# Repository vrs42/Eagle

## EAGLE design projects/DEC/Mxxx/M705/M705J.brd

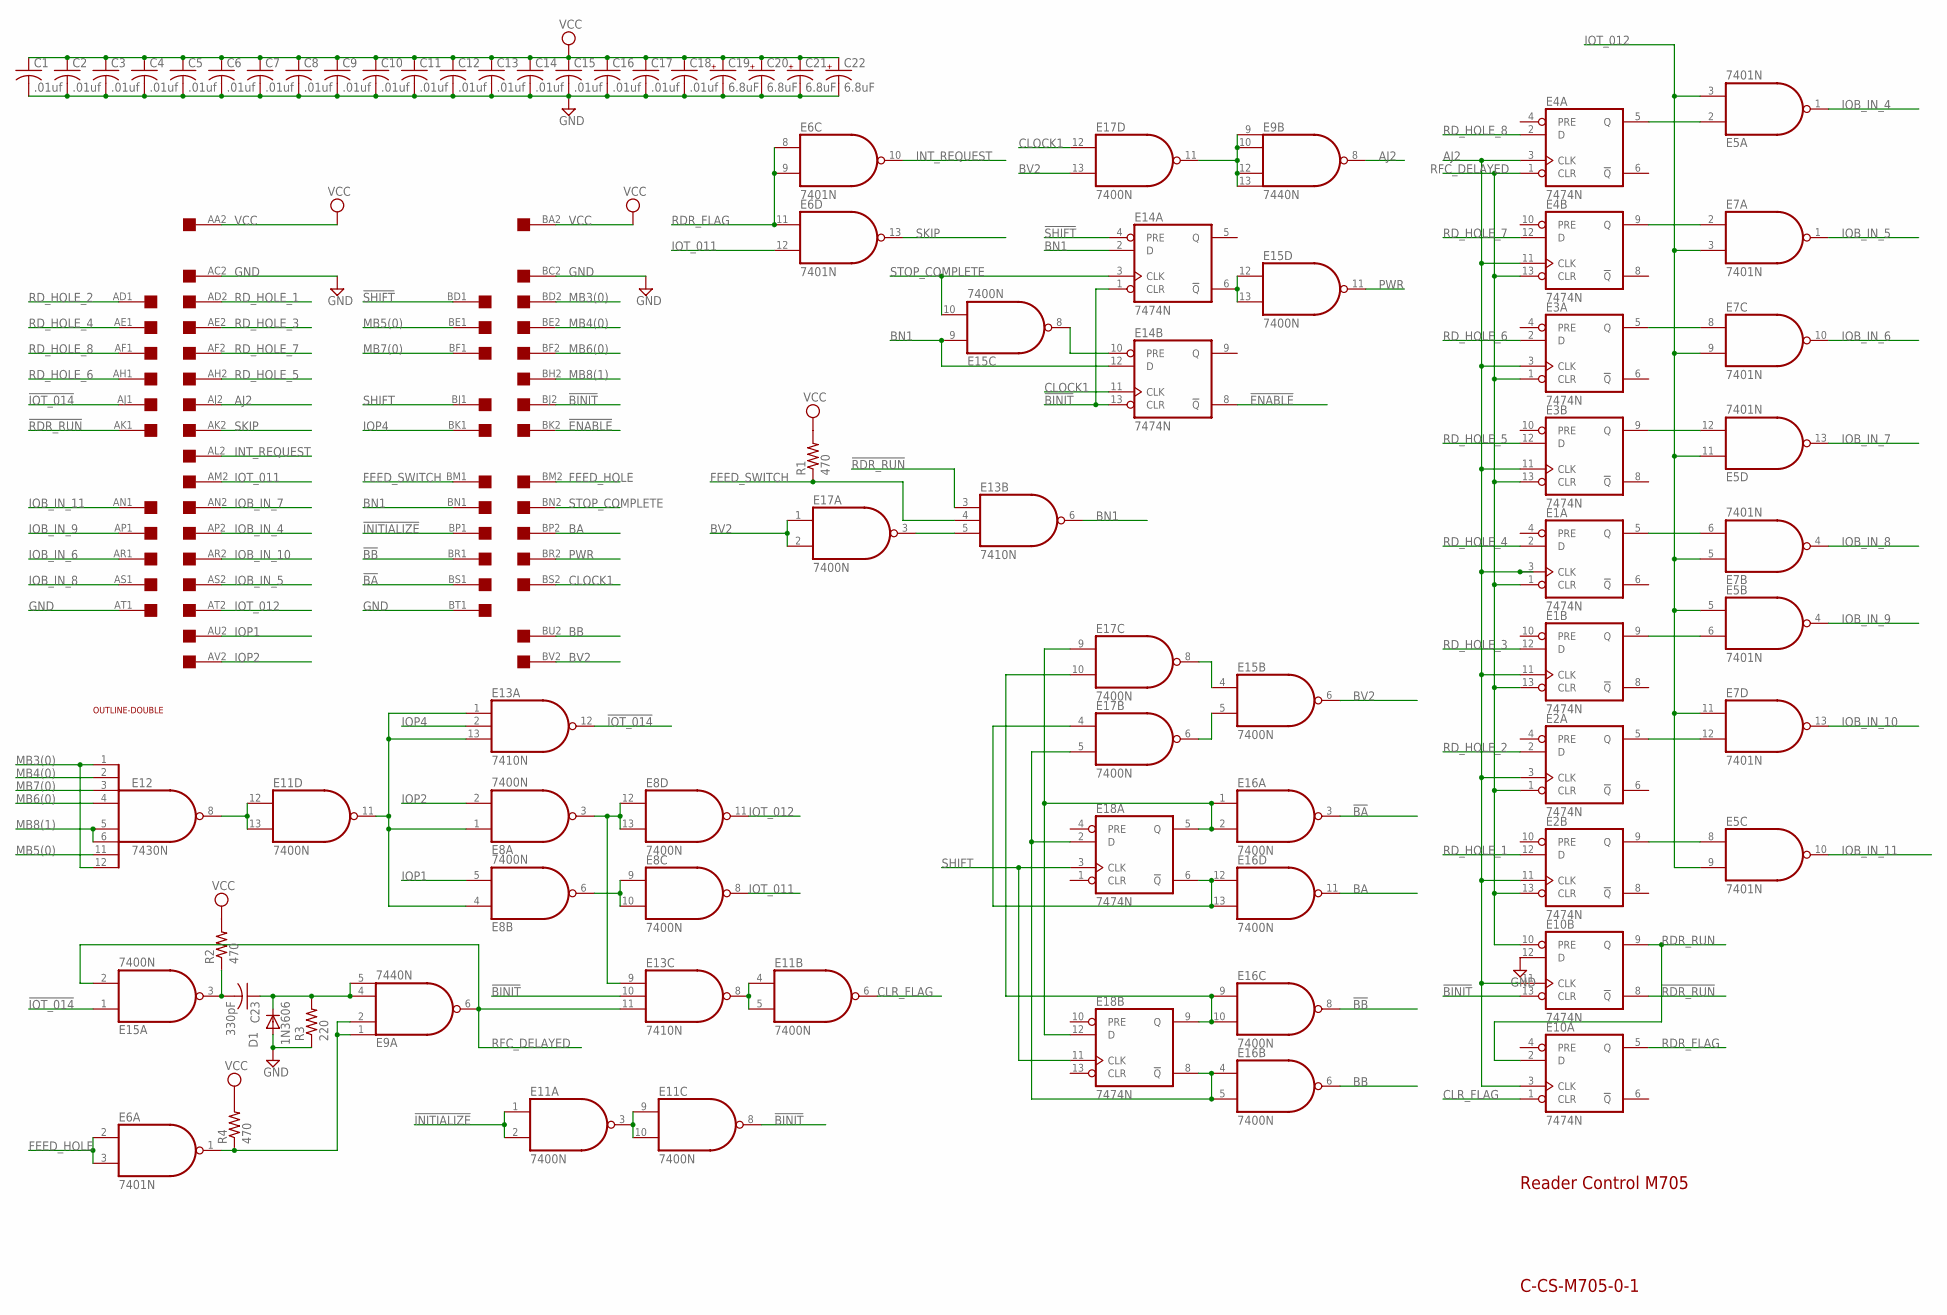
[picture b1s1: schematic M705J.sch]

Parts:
C1, C2, C3, C4, C5, C6, C7, C8, C9, C10, C11, C12, C13, C14, C15, C16, C17, C18: .01uf; C075-032X103
C19, C20, C21, C22: 6.8uF; E12-8
C23: 330pF; C075-032X103
D1: 1N3606; DO35-10
E1, E2, E3, E4, E10, E14, E18: 7474N; DIL14
E5, E6, E7: 7401N; DIL14
E8, E11, E15, E16, E17: 7400N; DIL14
E9: 7440N; DIL14
E12: 7430N; DIL14
E13: 7410N; DIL14
R1, R2, R4: 470; 0207/10
R3: 220; 0207/10
U$5: DOUBLE; EDGE-CON4
U$6: OUTLINE-DOUBLE; DOUBLE

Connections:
!BA: E16.3 (O), U$5.BS1
!BB: E16.8 (O), U$5.BR1
!BINIT: E10.13 (CLR), E11.8 (O), E13.10 (I1), E14.1 (CLR), E14.13 (CLR), U$5.BJ2
!ENABLE: E14.8 (!Q), U$5.BK2
!INITIALIZE: E11.1 (I0), E11.2 (I1), U$5.BP1
!IOT_014: E13.12 (O), E15.1 (I0), U$5.AJ1
!RDR_RUN: E10.8 (!Q), E13.3 (I0), U$5.AK1
!SHIFT: E14.4 (PRE), U$5.BD1
AJ2: E1.3 (CLK), E1.11 (CLK), E2.3 (CLK), E2.11 (CLK), E3.3 (CLK), E3.11 (CLK), E4.3 (CLK), E4.11 (CLK), E9.8 (O), E10.3 (CLK), E10.11 (CLK), U$5.AJ2
BA: E16.11 (O), U$5.BP2
BB: E16.6 (O), U$5.BU2
BN1: E13.6 (O), E14.2 (D), E14.12 (D), E15.9 (I0), U$5.BN1
BV2: E15.6 (O), E17.1 (I0), E17.2 (I1), E17.13 (I1), U$5.BV2
CLOCK1: E14.11 (CLK), E17.12 (I0), U$5.BS2
CLR_FLAG: E10.1 (CLR), E11.6 (O)
FEED_HOLE: E6.2 (I0), E6.3 (I1), U$5.BM2
FEED_SWITCH: E13.4 (I1), R1.1, U$5.BM1
GND: C1.2, C2.2, C3.2, C4.2, C5.2, C6.2, C7.2, C8.2, C9.2, C10.2, C11.2, C12.2, C13.2, C14.2, C15.2, C16.2, C17.2, C18.2, C19.-, C20.-, C21.-, C22.-, D1.A, E1.7 (GND), E2.7 (GND), E3.7 (GND), E4.7 (GND), E5.7 (GND), E6.7 (GND), E7.7 (GND), E8.7 (GND), E9.7 (GND), E10.7 (GND), E10.12 (D), E11.7 (GND), E12.7 (GND), E13.7 (GND), E14.7 (GND), E15.7 (GND), E16.7 (GND), E17.7 (GND), E18.7 (GND), R3.1, U$5.AC2, U$5.AT1, U$5.BC2, U$5.BT1
INT_REQUEST: E6.10 (O), U$5.AL2
IOB_IN_4: E5.1 (O), U$5.AP2
IOB_IN_5: E7.1 (O), U$5.AS2
IOB_IN_6: E7.10 (O), U$5.AR1
IOB_IN_7: E5.13 (O), U$5.AN2
IOB_IN_8: E7.4 (O), U$5.AS1
IOB_IN_9: E5.4 (O), U$5.AP1
IOB_IN_10: E7.13 (O), U$5.AR2
IOB_IN_11: E5.10 (O), U$5.AN1
IOP1: E8.5 (I1), U$5.AU2
IOP2: E8.2 (I1), U$5.AV2
IOP4: E13.2 (I1), U$5.BK1
IOT_011: E6.12 (I1), E8.8 (O), U$5.AM2
IOT_012: E5.3 (I1), E5.5 (I0), E5.9 (I1), E5.11 (I0), E7.3 (I1), E7.5 (I0), E7.9 (I1), E7.11 (I0), E8.11 (O), U$5.AT2
MB3(0): E12.1 (I0), E12.12 (I7), U$5.BD2
MB4(0): E12.2 (I1), U$5.BE2
MB5(0): E12.11 (I6), U$5.BE1
MB6(0): E12.4 (I3), U$5.BF2
MB7(0): E12.3 (I2), U$5.BF1
MB8(1): E12.5 (I4), E12.6 (I5), U$5.BH2
unnamed: E16.9 (I0), E16.10 (I1), E17.10 (I1), E18.9 (Q)
unnamed: E4.5 (Q), E5.2 (I0)
unnamed: E4.9 (Q), E7.2 (I0)
unnamed: E16.12 (I0), E16.13 (I1), E17.4 (I0), E18.6 (!Q)
unnamed: E11.12 (I0), E11.13 (I1), E12.8 (O)
unnamed: E8.3 (O), E8.12 (I0), E8.13 (I1), E13.9 (I0)
unnamed: E8.6 (O), E8.9 (I0), E8.10 (I1)
unnamed: E8.1 (I0), E8.4 (I0), E11.11 (O), E13.1 (I0), E13.13 (I2)
unnamed: E3.5 (Q), E7.8 (I0)
unnamed: E3.9 (Q), E5.12 (I1)
unnamed: E1.5 (Q), E7.6 (I1)
unnamed: E1.9 (Q), E5.6 (I1)
unnamed: E2.5 (Q), E7.12 (I1)
unnamed: E2.9 (Q), E5.8 (I0)
unnamed: E16.4 (I0), E16.5 (I1), E17.5 (I1), E18.2 (D), E18.8 (!Q)
unnamed: E16.1 (I0), E16.2 (I1), E17.9 (I0), E18.5 (Q), E18.12 (D)
unnamed: E15.4 (I0), E17.8 (O)
unnamed: E15.5 (I1), E17.6 (O)
unnamed: E9.9 (I0), E9.10 (I1), E9.12 (I2), E9.13 (I3), E17.11 (O)
unnamed: E14.6 (!Q), E15.12 (I0), E15.13 (I1)
unnamed: E14.10 (PRE), E15.8 (O)
unnamed: C23.2, E15.3 (O), R2.1
unnamed: C23.1, D1.C, E9.4 (I2), E9.5 (I3), R3.2
unnamed: E6.1 (O), E9.1 (I0), E9.2 (I1), R4.1
unnamed: E11.3 (O), E11.9 (I0), E11.10 (I1)
unnamed: E11.4 (I0), E11.5 (I1), E13.8 (O)
unnamed: E13.5 (I2), E17.3 (O)
PWR: E15.11 (O), U$5.BR2
RDR_FLAG: E6.8 (I0), E6.9 (I1), E6.11 (I0), E10.5 (Q)
RDR_RUN: E10.2 (D), E10.9 (Q)
RD_HOLE_1: E2.12 (D), U$5.AD2
RD_HOLE_2: E2.2 (D), U$5.AD1
RD_HOLE_3: E1.12 (D), U$5.AE2
RD_HOLE_4: E1.2 (D), U$5.AE1
RD_HOLE_5: E3.12 (D), U$5.AH2
RD_HOLE_6: E3.2 (D), U$5.AH1
RD_HOLE_7: E4.12 (D), U$5.AF2
RD_HOLE_8: E4.2 (D), U$5.AF1
RFC_DELAYED: E1.1 (CLR), E1.13 (CLR), E2.1 (CLR), E2.13 (CLR), E3.1 (CLR), E3.13 (CLR), E4.1 (CLR), E4.13 (CLR), E9.6 (O), E10.10 (PRE), E13.11 (I2), E15.2 (I1)
SHIFT: E18.3 (CLK), E18.11 (CLK), U$5.BJ1
SKIP: E6.13 (O), U$5.AK2
STOP_COMPLETE: E14.3 (CLK), E15.10 (I1), U$5.BN2
VCC: C1.1, C2.1, C3.1, C4.1, C5.1, C6.1, C7.1, C8.1, C9.1, C10.1, C11.1, C12.1, C13.1, C14.1, C15.1, C16.1, C17.1, C18.1, C19.+, C20.+, C21.+, C22.+, E1.14 (VCC), E2.14 (VCC), E3.14 (VCC), E4.14 (VCC), E5.14 (VCC), E6.14 (VCC), E7.14 (VCC), E8.14 (VCC), E9.14 (VCC), E10.14 (VCC), E11.14 (VCC), E12.14 (VCC), E13.14 (VCC), E14.14 (VCC), E15.14 (VCC), E16.14 (VCC), E17.14 (VCC), E18.14 (VCC), R1.2, R2.2, R4.2, U$5.AA2, U$5.BA2

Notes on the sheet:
C-CS-M705-0-1
Reader Control M705

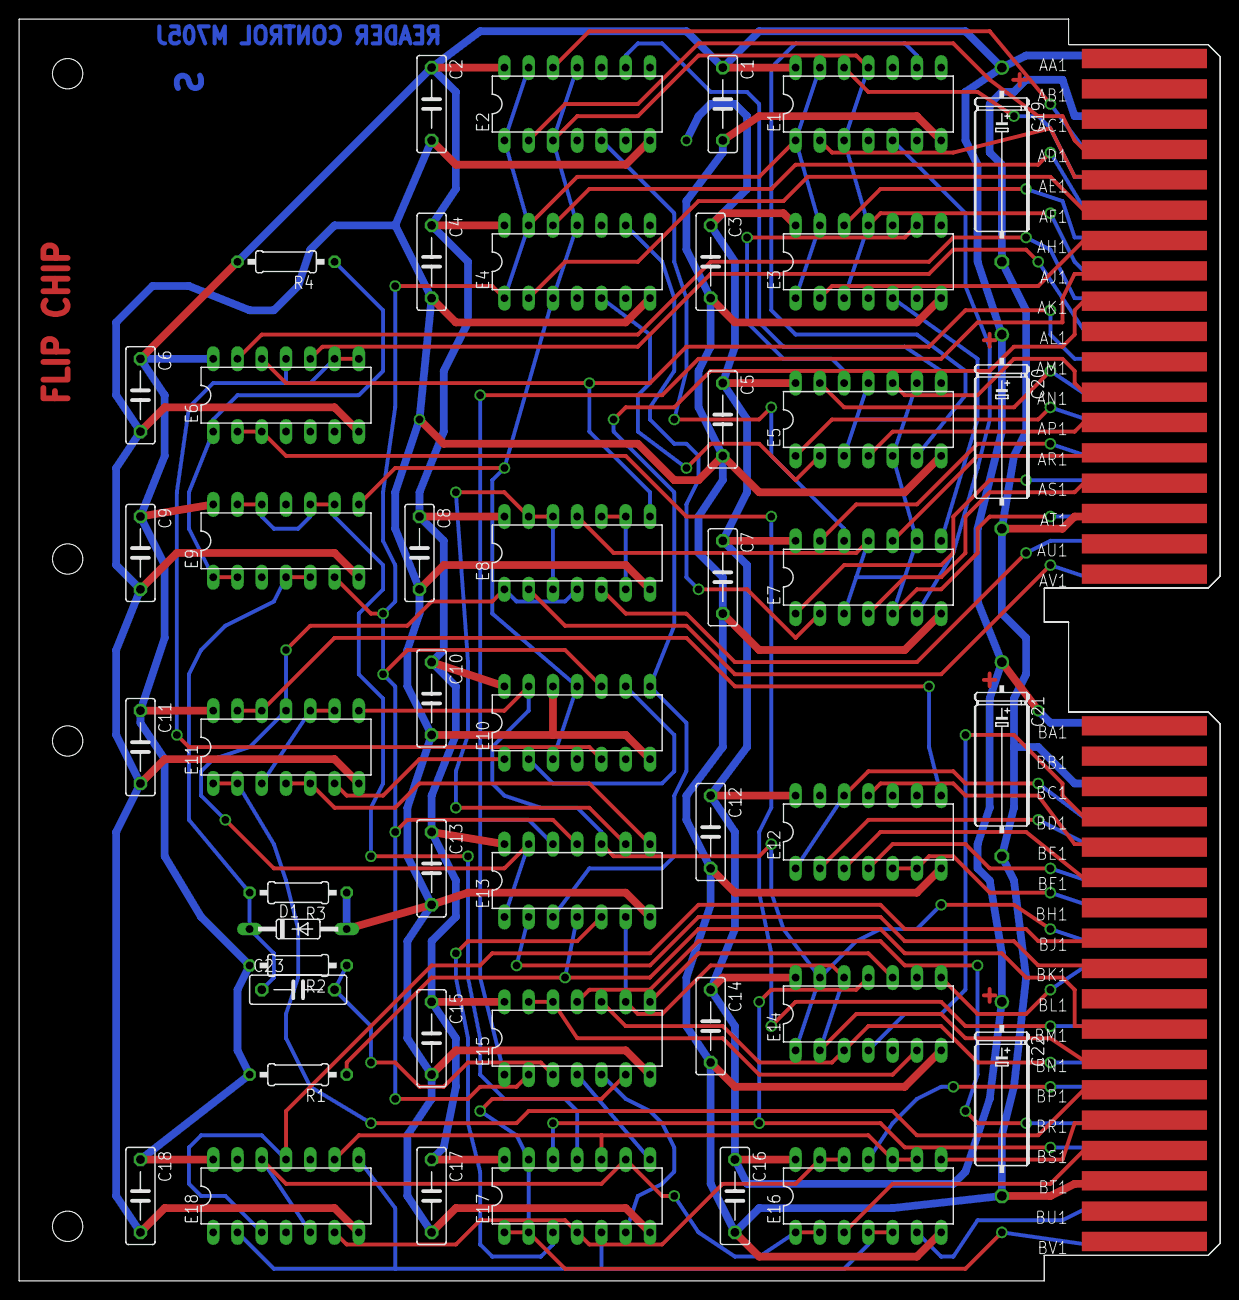
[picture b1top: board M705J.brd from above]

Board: 2 copper layers, 125.7 x 132.1 mm, 49 parts (0 on the bottom side), 81 nets.

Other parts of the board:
U$3: FLIPCHIP

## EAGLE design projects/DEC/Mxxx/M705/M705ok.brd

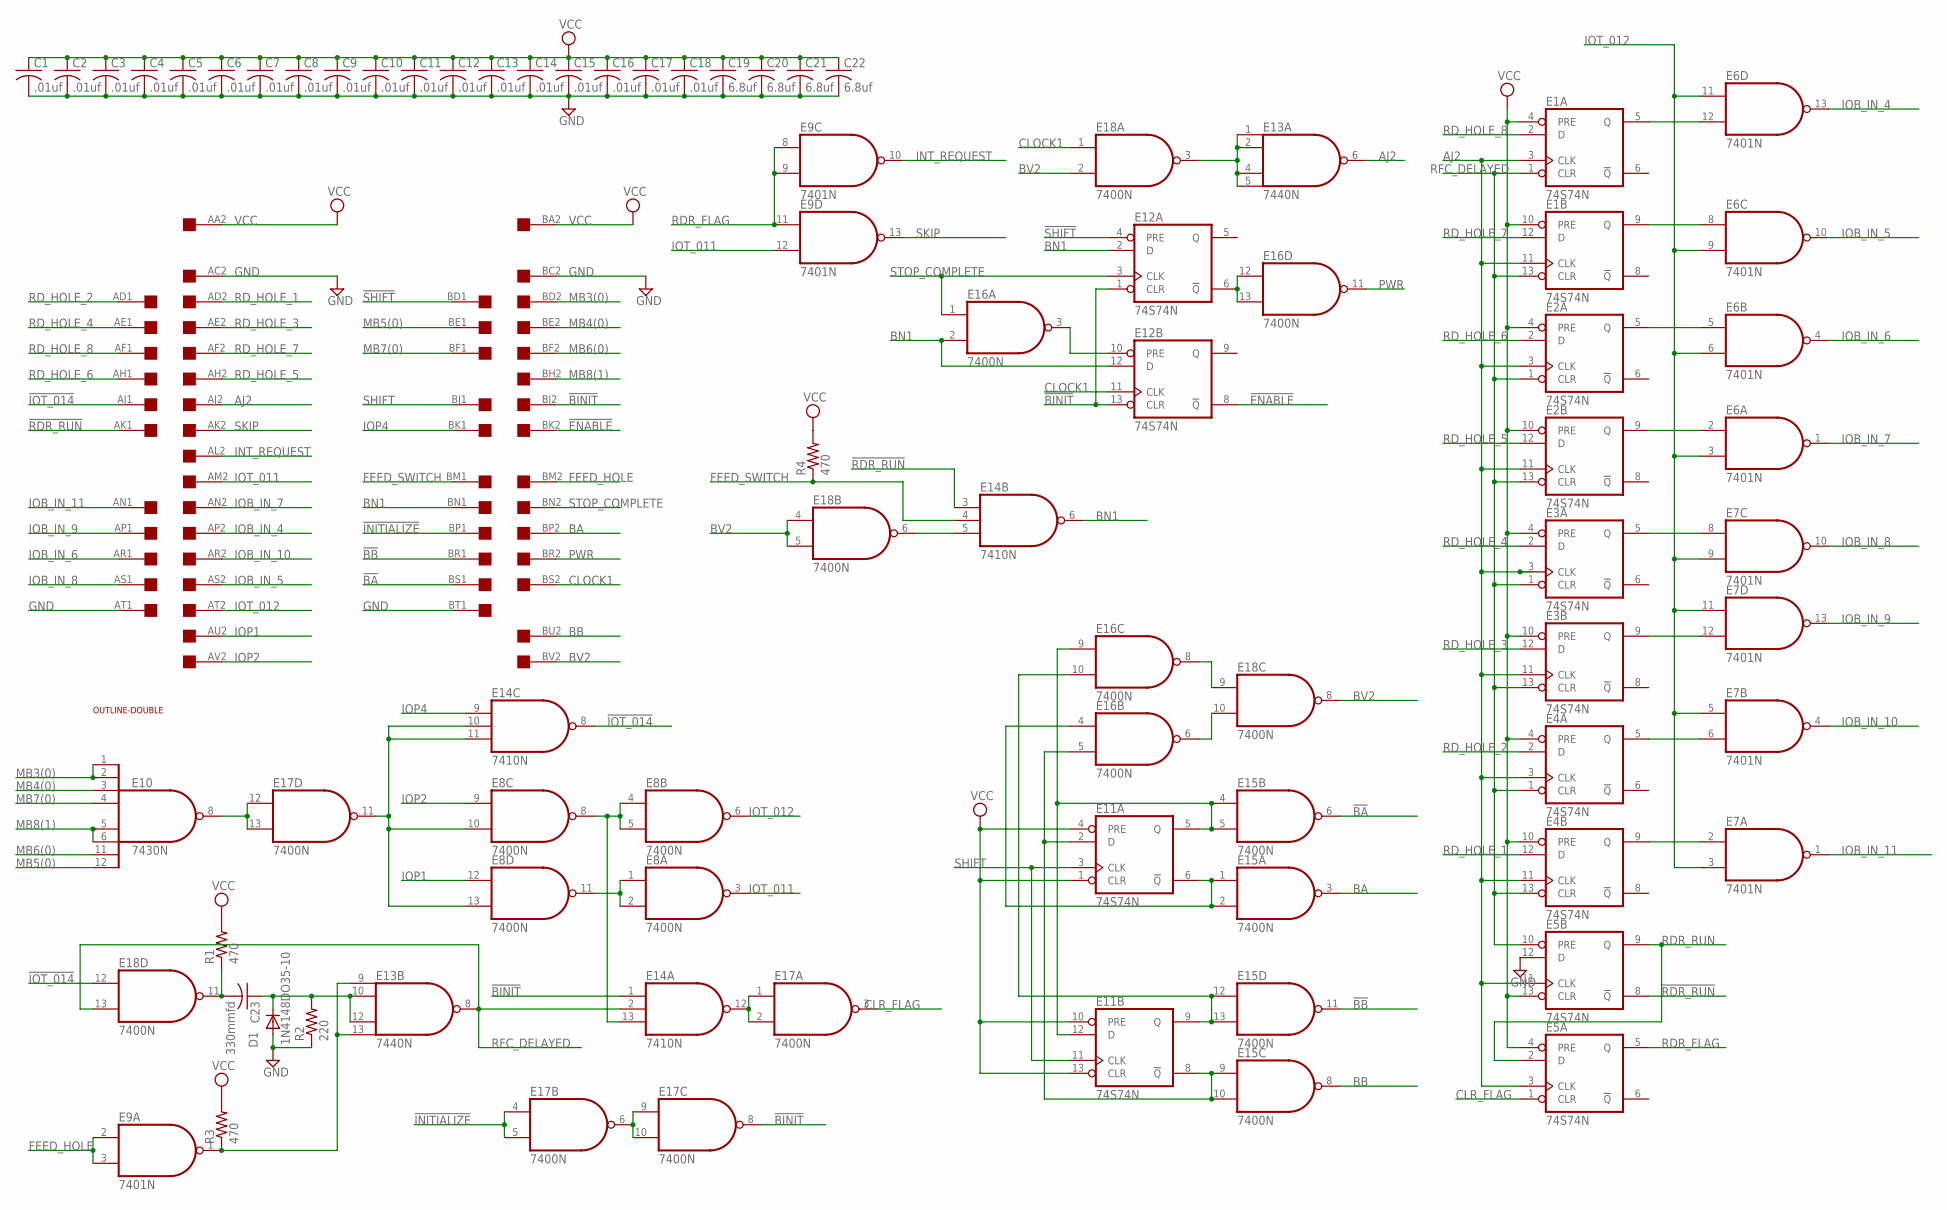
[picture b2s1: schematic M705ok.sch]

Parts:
C1, C2, C3, C4, C5, C6, C7, C8, C9, C10, C11, C12, C13, C14, C15, C16, C17, C18: .01uf; C050-025X075
C19, C20, C21, C22: 6.8uf; C150-054X183
C23: 330mmfd; C050-025X075
D1: 1N4148DO35-10; DO35-10
E1, E2, E3, E4, E5, E11, E12: 74S74N; DIL14
E6, E7, E9: 7401N; DIL14
E8, E15, E16, E17, E18: 7400N; DIL14
E10: 7430N; DIL14
E13: 7440N; DIL14
E14: 7410N; DIL14
R1, R3, R4: 470; 0207/10
R2: 220; 0207/10
U$5: DOUBLE; EDGE-CON4
U$6: OUTLINE-DOUBLE; DOUBLE

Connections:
!BA: E15.6 (O), U$5.BS1
!BB: E15.11 (O), U$5.BR1
!BINIT: E12.1 (CLR), E12.13 (CLR), E14.1 (I0), E17.8 (O), U$5.BJ2
!ENABLE: E12.8 (!Q), U$5.BK2
!INITIALIZE: E17.4 (I0), E17.5 (I1), U$5.BP1
!IOT_014: E14.8 (O), E18.12 (I0), U$5.AJ1
!RDR_RUN: E5.8 (!Q), E14.3 (I0), U$5.AK1
!SHIFT: E12.4 (PRE), U$5.BD1
AJ2: E1.3 (CLK), E1.11 (CLK), E2.3 (CLK), E2.11 (CLK), E3.3 (CLK), E3.11 (CLK), E4.3 (CLK), E4.11 (CLK), E5.3 (CLK), E5.11 (CLK), E13.6 (O), U$5.AJ2
BA: E15.3 (O), U$5.BP2
BB: E15.8 (O), U$5.BU2
BN1: E12.2 (D), E12.12 (D), E14.6 (O), E16.2 (I1), U$5.BN1
BV2: E18.2 (I1), E18.4 (I0), E18.5 (I1), E18.8 (O), U$5.BV2
CLOCK1: E12.11 (CLK), E18.1 (I0), U$5.BS2
CLR_FLAG: E5.1 (CLR), E17.3 (O)
FEED_HOLE: E9.2 (I0), E9.3 (I1), U$5.BM2
FEED_SWITCH: E14.4 (I1), R4.1, U$5.BM1
GND: C1.2, C2.2, C3.2, C4.2, C5.2, C6.2, C7.2, C8.2, C9.2, C10.2, C11.2, C12.2, C13.2, C14.2, C15.2, C16.2, C17.2, C18.2, C19.2, C20.2, C21.2, C22.2, D1.A, E1.7 (GND), E2.7 (GND), E3.7 (GND), E4.7 (GND), E5.7 (GND), E5.12 (D), E6.7 (GND), E7.7 (GND), E8.7 (GND), E9.7 (GND), E10.7 (GND), E11.7 (GND), E12.7 (GND), E13.7 (GND), E14.7 (GND), E15.7 (GND), E16.7 (GND), E17.7 (GND), E18.7 (GND), R2.1, U$5.AC2, U$5.AT1, U$5.BC2, U$5.BT1
INT_REQUEST: E9.10 (O), U$5.AL2
IOB_IN_4: E6.13 (O), U$5.AP2
IOB_IN_5: E6.10 (O), U$5.AS2
IOB_IN_6: E6.4 (O), U$5.AR1
IOB_IN_7: E6.1 (O), U$5.AN2
IOB_IN_8: E7.10 (O), U$5.AS1
IOB_IN_9: E7.13 (O), U$5.AP1
IOB_IN_10: E7.4 (O), U$5.AR2
IOB_IN_11: E7.1 (O), U$5.AN1
IOP1: E8.12 (I0), U$5.AU2
IOP2: E8.9 (I0), U$5.AV2
IOP4: E14.9 (I0), U$5.BK1
IOT_011: E8.3 (O), E9.12 (I1), U$5.AM2
IOT_012: E6.3 (I1), E6.6 (I1), E6.9 (I1), E6.11 (I0), E7.3 (I1), E7.5 (I0), E7.9 (I1), E7.11 (I0), E8.6 (O), U$5.AT2
MB3(0): E10.1 (I0), E10.2 (I1), U$5.BD2
MB4(0): E10.3 (I2), U$5.BE2
MB5(0): E10.12 (I7), U$5.BE1
MB6(0): E10.11 (I6), U$5.BF2
MB7(0): E10.4 (I3), U$5.BF1
MB8(1): E10.5 (I4), E10.6 (I5), U$5.BH2
unnamed: E1.5 (Q), E6.12 (I1)
unnamed: E1.9 (Q), E6.8 (I0)
unnamed: E11.6 (!Q), E15.1 (I0), E15.2 (I1), E16.4 (I0)
unnamed: E10.8 (O), E17.12 (I0), E17.13 (I1)
unnamed: E8.4 (I0), E8.5 (I1), E8.8 (O), E14.13 (I2)
unnamed: E8.1 (I0), E8.2 (I1), E8.11 (O)
unnamed: E8.10 (I1), E8.13 (I1), E14.10 (I1), E14.11 (I2), E17.11 (O)
unnamed: E2.5 (Q), E6.5 (I0)
unnamed: E2.9 (Q), E6.2 (I0)
unnamed: E3.5 (Q), E7.8 (I0)
unnamed: E3.9 (Q), E7.12 (I1)
unnamed: E4.5 (Q), E7.6 (I1)
unnamed: E4.9 (Q), E7.2 (I0)
unnamed: E11.5 (Q), E11.12 (D), E15.4 (I0), E15.5 (I1), E16.9 (I0)
unnamed: E11.9 (Q), E15.12 (I0), E15.13 (I1), E16.10 (I1)
unnamed: E11.2 (D), E11.8 (!Q), E15.9 (I0), E15.10 (I1), E16.5 (I1)
unnamed: E16.8 (O), E18.9 (I0)
unnamed: E16.6 (O), E18.10 (I1)
unnamed: E13.1 (I0), E13.2 (I1), E13.4 (I2), E13.5 (I3), E18.3 (O)
unnamed: E12.6 (!Q), E16.12 (I0), E16.13 (I1)
unnamed: E12.10 (PRE), E16.3 (O)
unnamed: C23.2, E18.11 (O), R1.1
unnamed: C23.1, D1.C, E13.10 (I1), E13.12 (I2), R2.2
unnamed: E9.1 (O), E13.9 (I0), E13.13 (I3), R3.1
unnamed: E17.6 (O), E17.9 (I0), E17.10 (I1)
unnamed: E14.12 (O), E17.1 (I0), E17.2 (I1)
unnamed: E14.5 (I2), E18.6 (O)
PWR: E16.11 (O), U$5.BR2
RDR_FLAG: E5.5 (Q), E9.8 (I0), E9.9 (I1), E9.11 (I0)
RDR_RUN: E5.2 (D), E5.9 (Q)
RD_HOLE_1: E4.12 (D), U$5.AD2
RD_HOLE_2: E4.2 (D), U$5.AD1
RD_HOLE_3: E3.12 (D), U$5.AE2
RD_HOLE_4: E3.2 (D), U$5.AE1
RD_HOLE_5: E2.12 (D), U$5.AH2
RD_HOLE_6: E2.2 (D), U$5.AH1
RD_HOLE_7: E1.12 (D), U$5.AF2
RD_HOLE_8: E1.2 (D), U$5.AF1
RFC_DELAYED: E1.1 (CLR), E1.13 (CLR), E2.1 (CLR), E2.13 (CLR), E3.1 (CLR), E3.13 (CLR), E4.1 (CLR), E4.13 (CLR), E5.10 (PRE), E13.8 (O), E14.2 (I1), E18.13 (I1)
SHIFT: E11.3 (CLK), E11.11 (CLK), U$5.BJ1
SKIP: E9.13 (O), U$5.AK2
STOP_COMPLETE: E12.3 (CLK), E16.1 (I0), U$5.BN2
VCC: C1.1, C2.1, C3.1, C4.1, C5.1, C6.1, C7.1, C8.1, C9.1, C10.1, C11.1, C12.1, C13.1, C14.1, C15.1, C16.1, C17.1, C18.1, C19.1, C20.1, C21.1, C22.1, E1.4 (PRE), E1.10 (PRE), E1.14 (VCC), E2.4 (PRE), E2.10 (PRE), E2.14 (VCC), E3.4 (PRE), E3.10 (PRE), E3.14 (VCC), E4.4 (PRE), E4.10 (PRE), E4.14 (VCC), E5.4 (PRE), E5.13 (CLR), E5.14 (VCC), E6.14 (VCC), E7.14 (VCC), E8.14 (VCC), E9.14 (VCC), E10.14 (VCC), E11.1 (CLR), E11.4 (PRE), E11.10 (PRE), E11.13 (CLR), E11.14 (VCC), E12.14 (VCC), E13.14 (VCC), E14.14 (VCC), E15.14 (VCC), E16.14 (VCC), E17.14 (VCC), E18.14 (VCC), R1.2, R3.2, R4.2, U$5.AA2, U$5.BA2

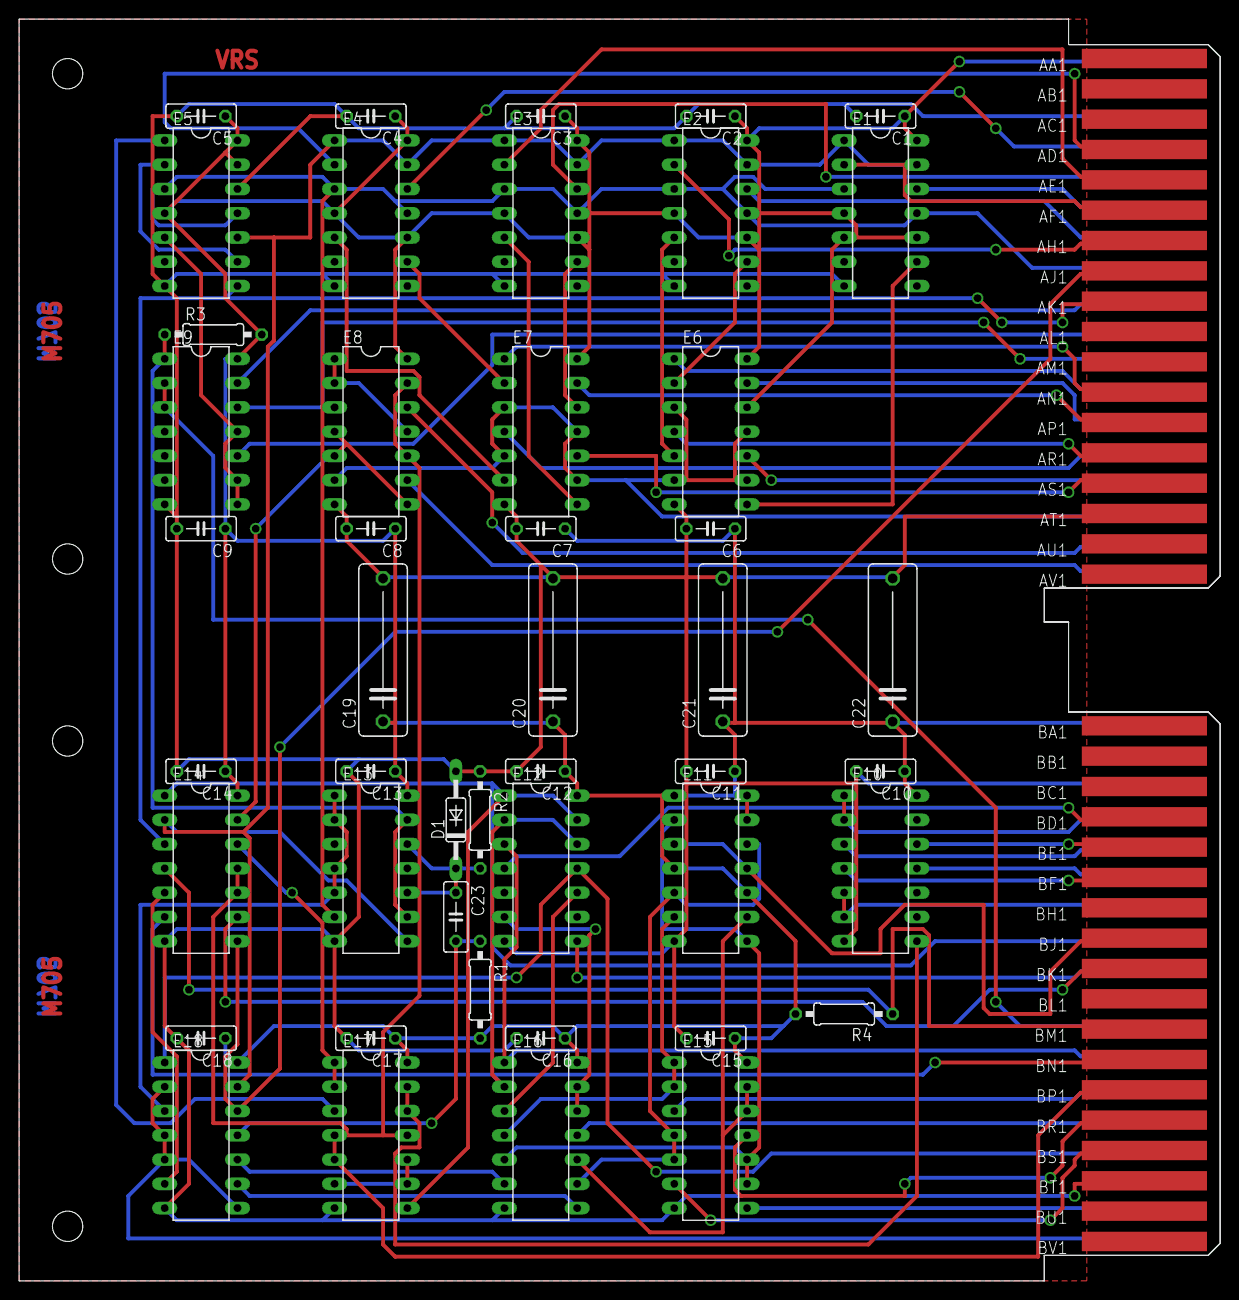
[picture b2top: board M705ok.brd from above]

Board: 2 copper layers, 125.7 x 132.1 mm, 48 parts (0 on the bottom side), 81 nets.

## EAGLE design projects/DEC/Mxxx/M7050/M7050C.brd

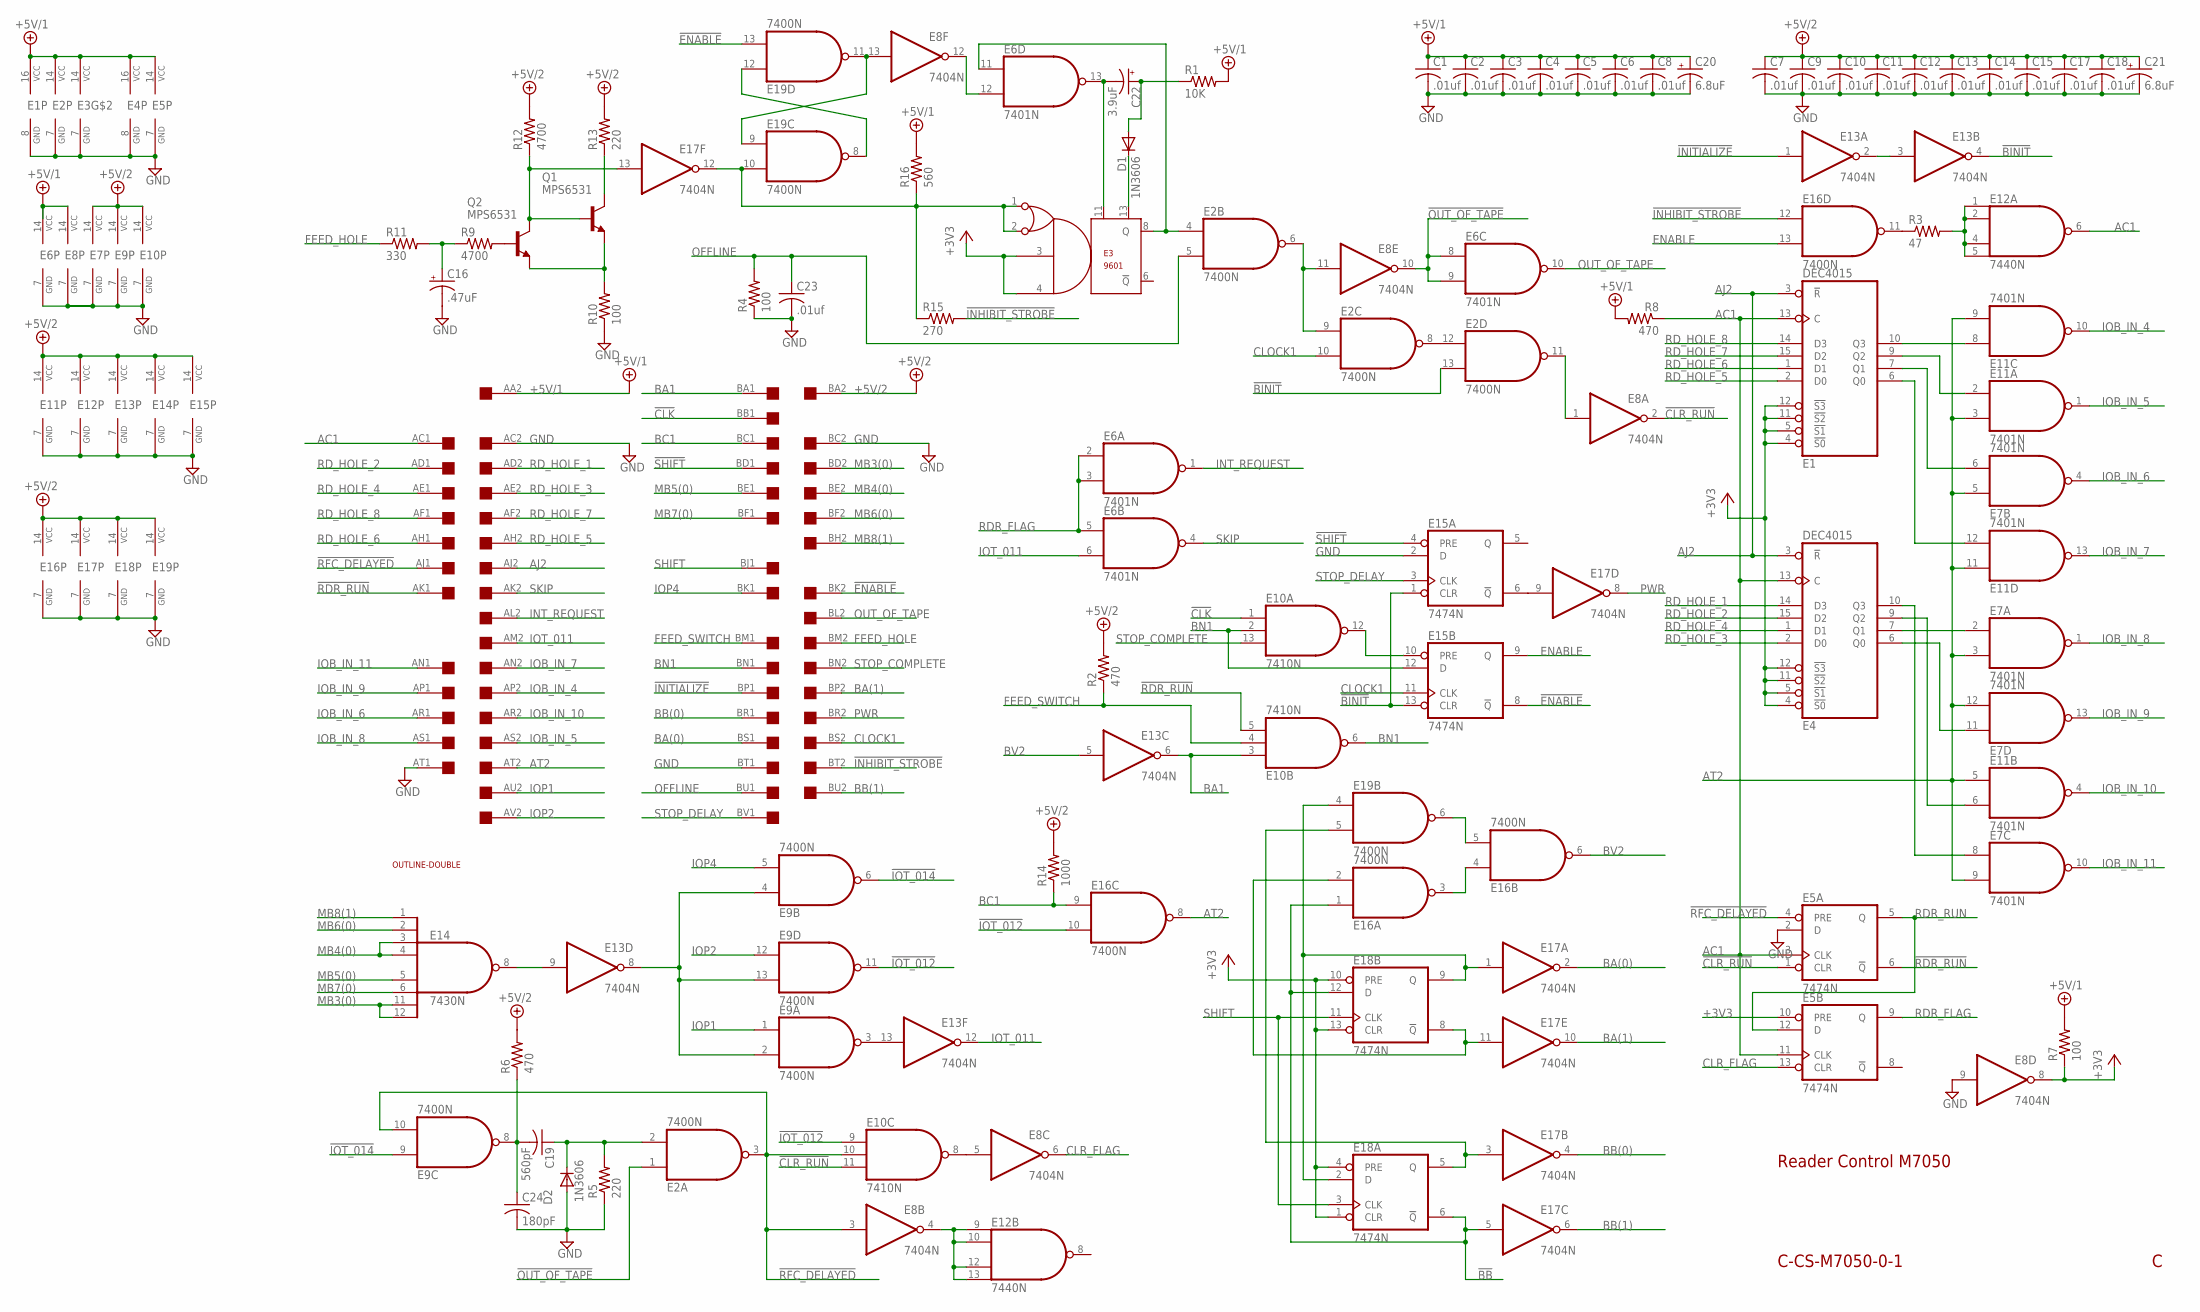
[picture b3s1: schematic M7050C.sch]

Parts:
C1, C2, C3, C4, C5, C6, C7, C8, C9, C10, C11, C12, C13, C14, C15, C17, C18, C23: .01uf; C075-032X103
C16: .47uF; E15-5
C19: 560pF; C075-032X103
C20, C21: 6.8uF; E12-8
C22: 3.9uF; E15-5
C24: 180pF; C075-032X103
D1, D2: 1N3606; DO35-10
E1, E4: DEC4015; DIL16
E2, E9, E16, E19: 7400N; DIL14
E3: 9601; DIL14
E5, E15, E18: 7474N; DIL14
E6, E7, E11: 7401N; DIL14
E8, E13, E17: 7404N; DIL14
E10: 7410N; DIL14
E12: 7440N; DIL14
E14: 7430N; DIL14
Q1, Q2: MPS6531; TO5
R1: 10K; 0207/10
R2, R6, R8: 470; 0207/10
R3: 47; 0207/10
R4, R7, R10: 100; 0207/10
R5, R13: 220; 0207/10
R9, R12: 4700; 0207/10
R11: 330; 0207/10
R14: 1000; 0207/10
R15: 270; 0207/10
R16: 560; 0207/10
U$5: DOUBLE; EDGE-CON4
U$6: OUTLINE-DOUBLE; DOUBLE

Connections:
!BA: E16.2 (I1), E17.11 (I), E18.8 (!Q)
!BB: E16.1 (I0), E17.5 (I), E18.6 (!Q), E18.12 (D)
!BINIT: E2.13 (I1), E13.4 (O), E15.1 (CLR), E15.13 (CLR)
!CLK: E10.1 (I0), U$5.BB1
!CLR_RUN: E5.1 (CLR), E8.2 (O), E10.11 (I2)
!ENABLE: E15.8 (!Q), E19.13 (I1), U$5.BK2
!INHIBIT_STROBE: E16.12 (I0), R15.2, U$5.BT2
!INITIALIZE: E13.1 (I), U$5.BP1
!IOT_011: E9.3 (O), E13.13 (I)
!IOT_012: E9.11 (O), E10.9 (I0), E16.10 (I1)
!IOT_014: E9.6 (O), E9.9 (I0)
!OUT_OF_TAPE: E2.1 (I0), E6.8 (I0), E6.9 (I1), E8.10 (O)
!RDR_RUN: E5.6 (!Q), E10.5 (I2), U$5.AK1
!RFC_DELAYED: E2.3 (O), E5.4 (PRE), E8.3 (I), E9.10 (I1), E10.10 (I1), U$5.AJ1
!SHIFT: E15.4 (PRE), U$5.BD1
+3V3: E1.4 (!S0), E1.5 (!S1), E1.11 (!S2), E1.12 (!S3), E3.3, E3.4, E4.4 (!S0), E4.5 (!S1), E4.11 (!S2), E4.12 (!S3), E5.10 (PRE), E8.8 (O), E18.1 (CLR), E18.4 (PRE), E18.10 (PRE), E18.13 (CLR), R7.1
+5V/1: C1.1, C2.1, C3.1, C4.1, C5.1, C6.1, C8.1, C20.+, E1.16 (VCC), E2.14 (VCC), E3.14 (VCC), E4.16 (VCC), E5.14 (VCC), E6.14 (VCC), E8.14 (VCC), R1.2, R7.2, R8.2, R16.2, U$5.AA2
+5V/2: C7.1, C9.1, C10.1, C11.1, C12.1, C13.1, C14.1, C15.1, C17.1, C18.1, C21.+, E7.14 (VCC), E9.14 (VCC), E10.14 (VCC), E11.14 (VCC), E12.14 (VCC), E13.14 (VCC), E14.14 (VCC), E15.14 (VCC), E16.14 (VCC), E17.14 (VCC), E18.14 (VCC), E19.14 (VCC), R2.2, R6.2, R12.2, R13.2, R14.2, U$5.BA2
AC1: E1.13 (C), E4.13 (C), E5.3 (CLK), E5.11 (CLK), E12.6 (O), R8.1, U$5.AC1
AJ2: E1.3 (!R), E4.3 (!R), U$5.AJ2
AT2: E7.3 (I1), E7.5 (I0), E7.9 (I1), E7.12 (I1), E11.3 (I1), E11.5 (I0), E11.9 (I1), E11.11 (I0), E16.8 (O), U$5.AT2
BA: E17.1 (I), E18.2 (D), E18.9 (Q), E19.4 (I0)
BA1: E10.3 (I0), E13.6 (O), U$5.BA1
BA(0): E17.2 (O), U$5.BS1
BA(1): E17.10 (O), U$5.BP2
BB: E17.3 (I), E18.5 (Q), E19.5 (I1)
BB(0): E17.4 (O), U$5.BR1
BB(1): E17.6 (O), U$5.BU2
BC1: E16.9 (I0), R14.1, U$5.BC1
BN1: E10.2 (I1), E10.6 (O), E15.12 (D), U$5.BN1
BV2: E13.5 (I), E16.6 (O)
CLOCK1: E2.10 (I1), E15.11 (CLK), U$5.BS2
CLR_FLAG: E5.13 (CLR), E8.6 (O)
ENABLE: E15.9 (Q), E16.13 (I1)
FEED_HOLE: R11.1, U$5.BM2
FEED_SWITCH: E10.4 (I1), R2.1, U$5.BM1
GND: C1.2, C2.2, C3.2, C4.2, C5.2, C6.2, C7.2, C8.2, C9.2, C10.2, C11.2, C12.2, C13.2, C14.2, C15.2, C16.-, C17.2, C18.2, C20.-, C21.-, C23.2, C24.2, D2.A, E1.8 (GND), E2.7 (GND), E3.7 (GND), E4.8 (GND), E5.2 (D), E5.7 (GND), E6.7 (GND), E7.7 (GND), E8.7 (GND), E8.9 (I), E9.7 (GND), E10.7 (GND), E11.7 (GND), E12.7 (GND), E13.7 (GND), E14.7 (GND), E15.2 (D), E15.7 (GND), E16.7 (GND), E17.7 (GND), E18.7 (GND), E19.7 (GND), R4.1, R5.1, R10.1, U$5.AC2, U$5.AT1, U$5.BC2, U$5.BT1
INT_REQUEST: E6.1 (O), U$5.AL2
IOB_IN_4: E11.10 (O), U$5.AP2
IOB_IN_5: E11.1 (O), U$5.AS2
IOB_IN_6: E7.4 (O), U$5.AR1
IOB_IN_7: E11.13 (O), U$5.AN2
IOB_IN_8: E7.1 (O), U$5.AS1
IOB_IN_9: E7.13 (O), U$5.AP1
IOB_IN_10: E11.4 (O), U$5.AR2
IOB_IN_11: E7.10 (O), U$5.AN1
IOP1: E9.1 (I0), U$5.AU2
IOP2: E9.12 (I0), U$5.AV2
IOP4: E9.5 (I1), U$5.BK1
IOT_011: E6.6 (I1), E13.12 (O), U$5.AM2
MB3(0): E14.11 (I6), E14.12 (I7), U$5.BD2
MB4(0): E14.3 (I2), E14.4 (I3), U$5.BE2
MB5(0): E14.5 (I4), U$5.BE1
MB6(0): E14.2 (I1), U$5.BF2
MB7(0): E14.6 (I5), U$5.BF1
MB8(1): E14.1 (I0), U$5.BH2
unnamed: D1.C, E3.13
unnamed: E1.10 (Q3), E11.8 (I0)
unnamed: E1.9 (Q2), E11.2 (I0)
unnamed: C22.+, D1.A, R1.1
unnamed: E13.9 (I), E14.8 (O)
unnamed: E2.11 (O), E8.1 (I)
unnamed: E9.2 (I1), E9.4 (I0), E9.13 (I1), E13.8 (O)
unnamed: E1.7 (Q1), E7.6 (I1)
unnamed: E1.6 (Q0), E11.12 (I1)
unnamed: E4.7 (Q1), E7.2 (I0)
unnamed: E4.6 (Q0), E7.11 (I0)
unnamed: E4.9 (Q2), E11.6 (I1)
unnamed: E4.10 (Q3), E7.8 (I0)
unnamed: E2.8 (O), E2.12 (I0)
unnamed: E17.13 (I), Q1.2 (B), Q2.3 (C), R12.1
unnamed: Q1.3 (C), R13.1
unnamed: Q1.1 (E), Q2.1 (E), R10.2
unnamed: Q2.2 (B), R9.2
unnamed: E3.1, E3.2, E17.12 (O), E19.10 (I1), R15.1, R16.1
unnamed: C16.+, R9.1, R11.2
unnamed: E16.5 (I1), E19.6 (O)
unnamed: E16.3 (O), E16.4 (I0)
unnamed: E16.11 (O), R3.1
unnamed: E15.6 (!Q), E17.9 (I)
unnamed: E10.12 (O), E15.10 (PRE)
unnamed: C19.2, C24.1, E9.8 (O), R6.1
unnamed: C19.1, D2.C, E2.2 (I1), R5.2
unnamed: E13.2 (O), E13.3 (I)
unnamed: E8.5 (I), E10.8 (O)
unnamed: E2.4 (I0), E3.8 (Q), E6.11 (I0)
unnamed: E2.6 (O), E2.9 (I0), E8.11 (I)
unnamed: E8.4 (O), E12.9 (I0), E12.10 (I1), E12.12 (I2), E12.13 (I3)
unnamed: C22.-, E3.11, E6.13 (O)
unnamed: E6.12 (I1), E8.12 (O)
unnamed: E12.1 (I0), E12.2 (I1), E12.4 (I2), E12.5 (I3), R3.2
unnamed: E8.13 (I), E19.9 (I0), E19.11 (O)
unnamed: E19.8 (O), E19.12 (I0)
OFFLINE: C23.1, E2.5 (I1), R4.2, U$5.BU1
OUT_OF_TAPE: E6.10 (O), U$5.BL2
PWR: E17.8 (O), U$5.BR2
RDR_FLAG: E5.9 (Q), E6.2 (I0), E6.3 (I1), E6.5 (I0)
RDR_RUN: E5.5 (Q), E5.12 (D)
RD_HOLE_1: E4.14 (D3), U$5.AD2
RD_HOLE_2: E4.15 (D2), U$5.AD1
RD_HOLE_3: E4.2 (D0), U$5.AE2
RD_HOLE_4: E4.1 (D1), U$5.AE1
RD_HOLE_5: E1.2 (D0), U$5.AH2
RD_HOLE_6: E1.1 (D1), U$5.AH1
RD_HOLE_7: E1.15 (D2), U$5.AF2
RD_HOLE_8: E1.14 (D3), U$5.AF1
SHIFT: E18.3 (CLK), E18.11 (CLK), U$5.BJ1
SKIP: E6.4 (O), U$5.AK2
STOP_COMPLETE: E10.13 (I2), U$5.BN2
STOP_DELAY: E15.3 (CLK), U$5.BV1

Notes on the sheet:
C-CS-M7050-0-1
Reader Control M7050

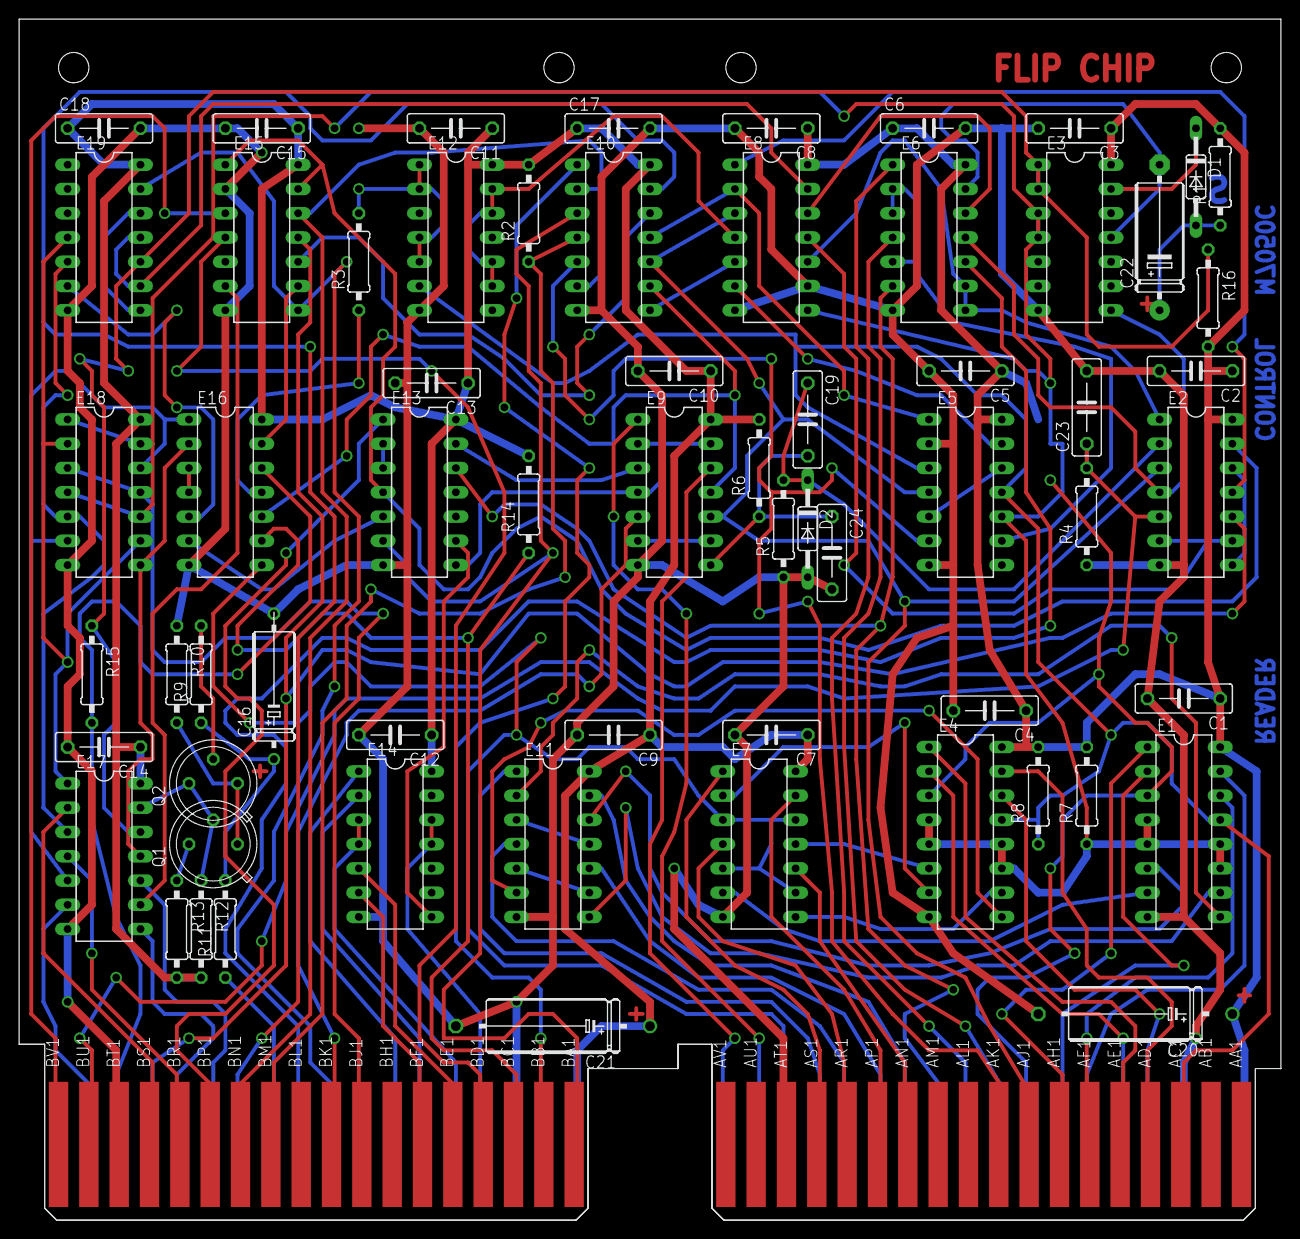
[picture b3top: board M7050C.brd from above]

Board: 2 copper layers, 132.1 x 125.7 mm, 66 parts (0 on the bottom side), 110 nets.

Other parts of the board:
U$3: FLIPCHIP
